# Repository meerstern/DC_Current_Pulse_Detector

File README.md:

# DC電流パルス検知基板
DC Current Pulse Detector with CT Sensor

## 概要 
  * 直流信号線のON、OFF状態をクランプ式CTセンサで検出するための変換基板です 
  * 本変換基板とクランプ式CTセンサによって信号線を加工せずに直流信号線の状態を取得することができます  
  * 信号線ON/OFFによって発生するパルスをCTセンサで検出し、状態をラッチします 
  * ラッチ保持した状態(信号線のON/OFF状態)を1/0のデジタル信号として出力します  
  * 基板上の可変抵抗で状態を切り替えるパルス閾値を変更することができます  
  * 3000:1の巻き線比のCTセンサを同梱しています  一般的なCTセンサでも置き換え可能です  
  * 信号線の電流に応じて閾値を変更することで5mA~50mA程度の信号線のON/OFF状態を出力できます  
  * 微弱な電流で誤検知する場合はCTセンサに信号線を複数回巻いて閾値を高く設定してください  
  * 電源3.0V~5.5V、コネクタはGrove互換コネクタです 
  * 出力はSTA1、STA2の2つあり、閾値が正しく設定されている場合、どちらか一方がONでもう片方はOFFとなります
  * STA1、STA2のON状態(LED D1とD2に対応)と信号線のON状態はCTセンサの向きによって変わります  
  * 基板サイズ30 x25mm、固定穴M3 x2 幅19mm  
  * 下記の図に示す様にCTセンサ白線をJ1の1番ピン、CTセンサ黒線J1の2番ピンに配線し、CTセンサのK→Ｌ電流を流した場合、  
  信号線ONでS1(LED1)がHighかつS2(LED2)がLowとなります。逆に信号線OFFでS1(LED1)がLowかつS2(LED2)がHighとなります。  

## 注意
  * 電源投入直後のデジタル出力状態は不定です  
  * 信号線ON/OFFによって発生するパルスの向きでON、OFFを検知するため、電源投入直後はSTA1、STA2の状態と信号状態が一致しません  
  * 電源投入後に信号線のONとOFFを1回繰り返すことで以降の信号線のON/OFF状態を保持して信号の状態をデジタル出力します  
  * 微弱な直流信号状態をCTセンサで簡易的に取得することを目的としており、10A以上の大電流のON/OFFの検出には使用しないでください  
  * 直流信号線のON/OFFの立上がり、立下りの勾配が緩やかな場合は検知できない場合があります  
  * STA1、STA2の両方がON状態の場合は閾値が正しく設定されていないため、可変抵抗を調整してください  
  * 信号線の電流が5mA前後の小さい場合やCTセンサの設置環境、配線の引き回し等の影響で誤検知する場合があります  
  * ノイズが多い環境では誤検知する可能性があります  ノイズ源から距離を保ち、CTセンサのケーブル長さを短くする等の対策を行ってください  
  * 信号状態を簡易的に取得することを目的としており、信頼性が求められる目的で使用しないでください  
  * 同梱CTセンサ(巻き線比3000:1,75A/25mA,7.5V以上保護 KCT-10)は納品タイミングによって予告なしに変更する場合があります  
  
## 販売サイト
  * [スイッチサイエンス][2]  

  MIT Lisense

[2]: https://www.switch-science.com/products/7396

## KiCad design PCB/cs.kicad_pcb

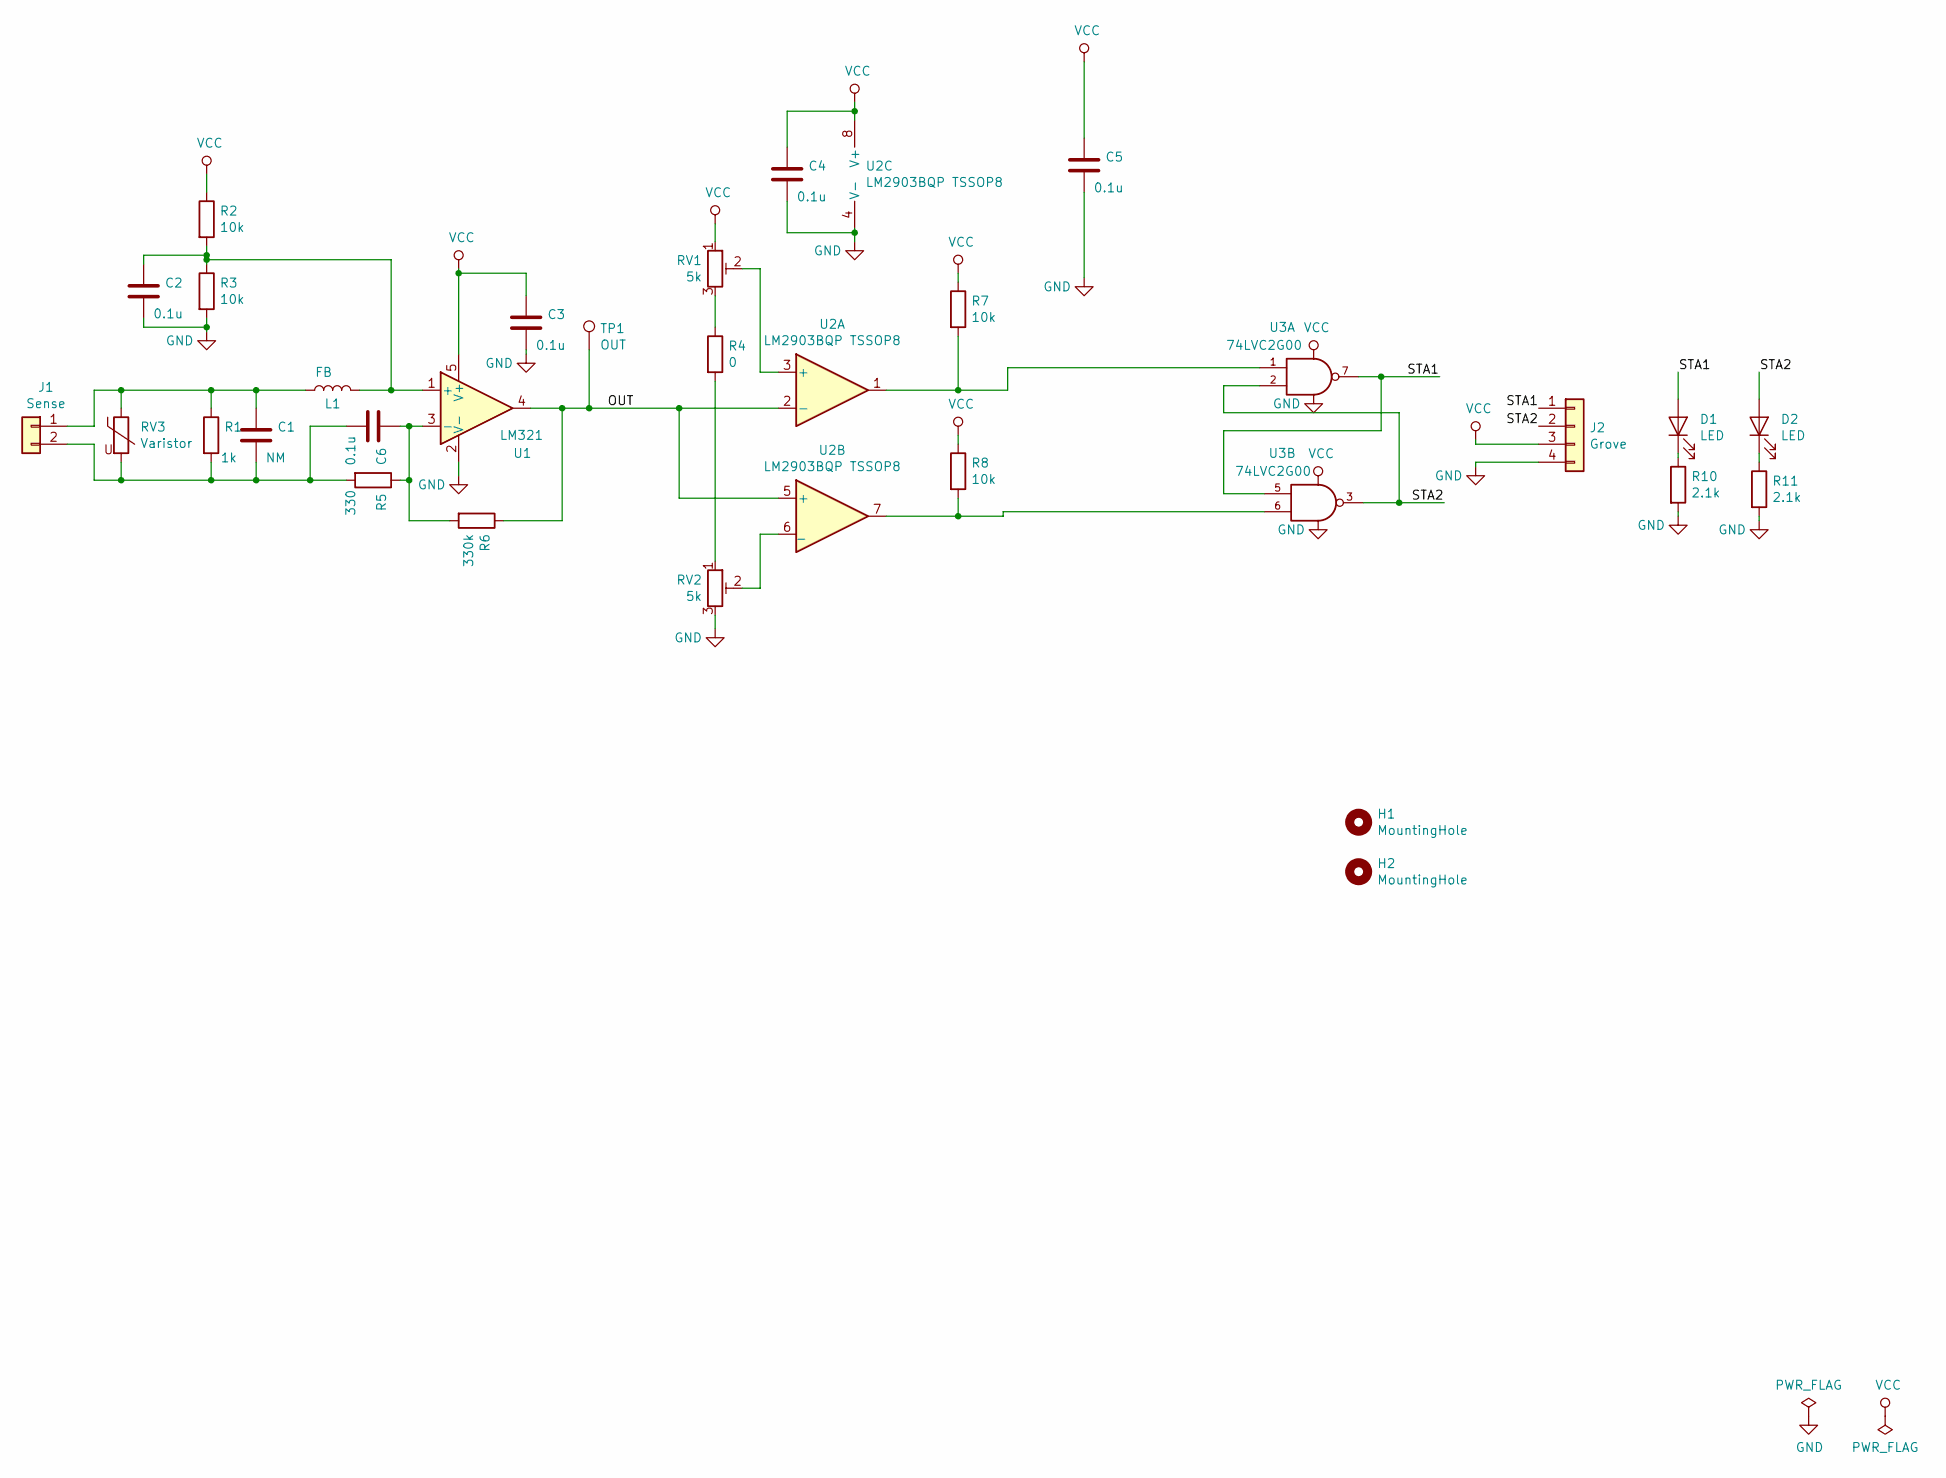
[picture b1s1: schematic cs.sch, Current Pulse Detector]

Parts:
C1: NM; C_0603_1608Metric
C2, C3, C4, C5, C6: 0.1u; C_0603_1608Metric
D1, D2: LED; LED_0603_1608Metric
H1, H2: MountingHole; MountingHole_3.2mm_M3
J1: Sense; TerminalBlock_bornier-2_P5.08mm
J2: Grove; GROVE
L1: FB; L_0603_1608Metric
R1: 1k; R_0603_1608Metric
R2, R3, R7, R8: 10k; R_0603_1608Metric
R4: 0; R_0603_1608Metric
R5: 330; R_0603_1608Metric
R6: 330k; R_0603_1608Metric
R10, R11: 2.1k; R_0603_1608Metric
RV1, RV2: 5k; rcl-RTRIMCVR42A
RV3: Varistor; Fuse_0402_1005Metric
TP1: OUT; TestPoint_Pad_D1.0mm
U1: LM321; SOT-23-5
U2: LM2903BQP TSSOP8; TSSOP-8_4.4x3mm_P0.65mm
U3: 74LVC2G00; TSSOP-8_3x3mm_P0.65mm

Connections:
/OUT: R6.1, TP1.1, U1.4, U2.2 (-), U2.5 (+)
/STA1: D1.2 (A), J2.1, U3.5, U3.7
/STA2: D2.2 (A), J2.2, U3.2, U3.3
GND: C2.2, C3.2, C4.2, C5.2, J2.4, R3.2, R10.2, R11.2, RV2.3, U1.2 (V-), U2.4 (V-), U3.4 (GND)
unnamed: C1.1, J1.1, L1.1, R1.1, RV3.1
unnamed: C1.2, C6.2, J1.2, R1.2, R5.2, RV3.2
unnamed: C2.1, L1.2, R2.2, R3.1, U1.1 (+)
unnamed: C6.1, R5.1, R6.2, U1.3 (-)
unnamed: D1.1 (K), R10.1
unnamed: D2.1 (K), R11.1
unnamed: R4.1, RV1.3
unnamed: R4.2, RV2.1
unnamed: R7.2, U2.1, U3.1
unnamed: R8.2, U2.7, U3.6
unnamed: RV1.2, U2.3 (+)
unnamed: RV2.2, U2.6 (_)
VCC: C3.1, C4.1, C5.1, J2.3, R2.1, R7.1, R8.1, RV1.1, U1.5 (V+), U2.8 (V+), U3.8 (VCC)

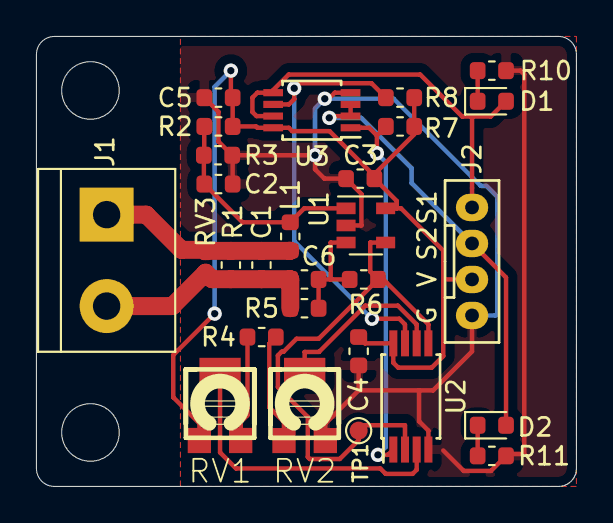
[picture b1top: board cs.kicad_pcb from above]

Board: 2 copper layers, 30.0 x 25.0 mm, 30 parts (0 on the bottom side), 17 nets.

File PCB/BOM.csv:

Elecrow PN,Parts,Value,Package,QTY,Digikey/Mouser/Manufacturer Part,Remark/ Link
,U2,LM2903BQP TSSOP8,TSSOP-8_4.4x3mm_P0.65mm,1,771-LVC2G00DP125 ,
,U3,74LVC2G00,TSSOP-8_3x3mm_P0.65mm,1,595-LM2903BIPWR,
,RV3,Varistor,Fuse_0402_1005Metric,1,810-AVR-M1005C080MC,
C22775,R4,100,R_0603_1608Metric,1,,
,J2,Grove,GROVE,1,713-110990037,
,L1,FB,L_0603_1608Metric,1,81-BLM18SG331TN1D,
C14663,"C5,C4,C3,C2",0.1u,C_0603_1608Metric,4,,
,U1,LM321,SOT-23-5,1,595-LM321LVIDBVR,
,"RV2,RV1",5k,rcl-RTRIMCVR42A,2,652-TC33X-2-502G,
C25804,"R8,R7,R3,R2",10k,R_0603_1608Metric,4,,
C23137,R6,330k,R_0603_1608Metric,1,,
C21190,R1,1k,R_0603_1608Metric,1,,
C4190,"R11,R10",2.2k,R_0603_1608Metric,2,,
4040806A,"D2,D1",LED,LED_0603_1608Metric,2,,
,J1,Sense,TerminalBlock_bornier-2_P5.08mm,1,490-TB007-508-02BE,
C23138,R5,330,R_0603_1608Metric,1,,

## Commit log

2021-06-30 Add PCB Files
2021-07-09 Add README
2021-07-09 Add an image
2021-07-27 Add images
2022-12-06 Add shop link
